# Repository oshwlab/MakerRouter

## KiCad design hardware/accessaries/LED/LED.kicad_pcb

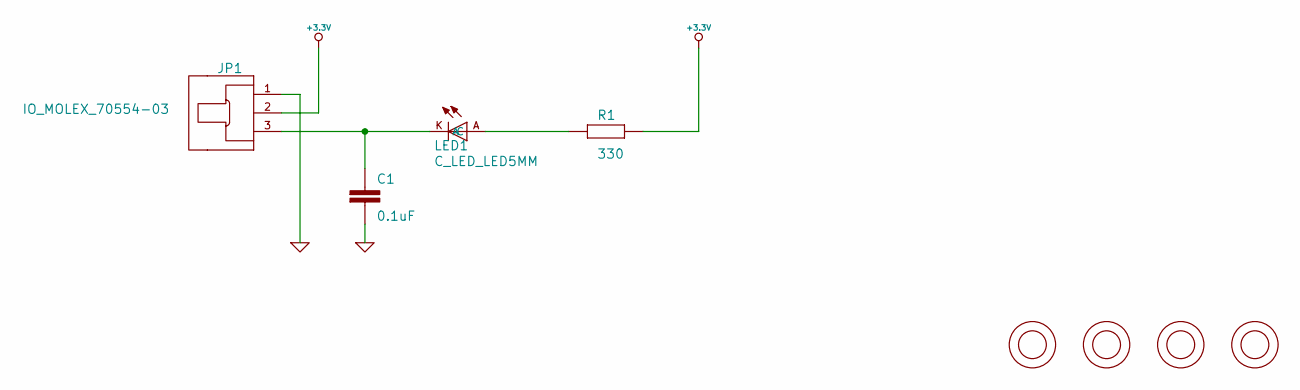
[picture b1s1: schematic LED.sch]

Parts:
C1: 0.1uF; C_C_0805
JP1: IO_MOLEX_70554-03
LED1: C_LED_LED5MM
P1, P2, P3, P4: IO_HOLE-3.2
R1: 330; C_R_0805

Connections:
+3.3V: JP1.2, R1.2
GND: C1.2, JP1.1
unnamed: LED1.A, R1.1
unnamed: C1.1, JP1.3, LED1.K (C)

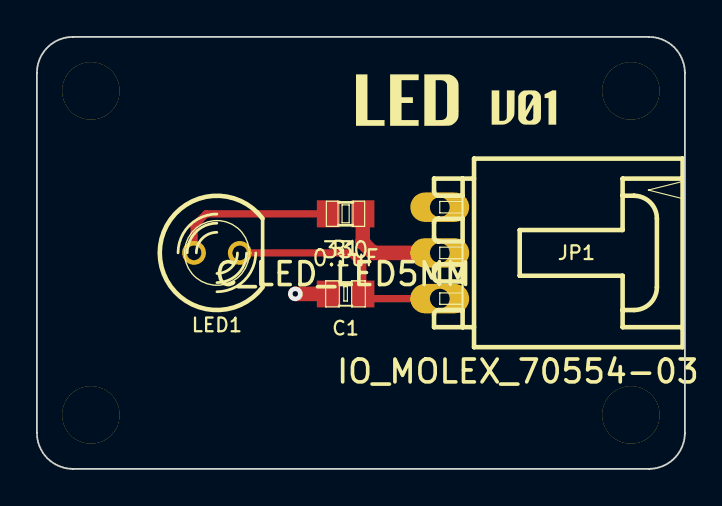
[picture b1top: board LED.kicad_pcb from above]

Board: 2 copper layers, 36.0 x 24.0 mm, 9 parts (1 on the bottom side), 4 nets.

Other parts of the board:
VAL: mini6

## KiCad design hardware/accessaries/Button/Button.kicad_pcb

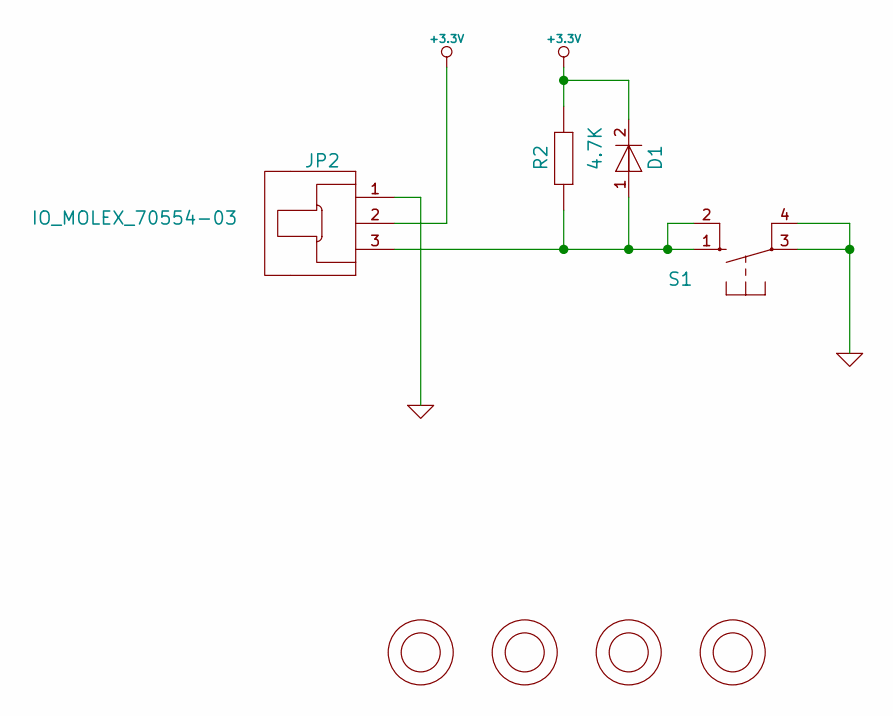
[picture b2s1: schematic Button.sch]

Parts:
D1: C_DIODE-1N4148_MINIMELF
JP2: IO_MOLEX_70554-03
P5, P6, P7, P8: IO_HOLE-3.2
R2: 4.7K; C_R_0805
S1: C_SW_OMRON-10-XX; switch-omron-B3F-40XX

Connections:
+3.3V: D1.2, JP2.2, R2.2
GND: JP2.1, S1.3, S1.4
unnamed: D1.1, JP2.3, R2.1, S1.1, S1.2

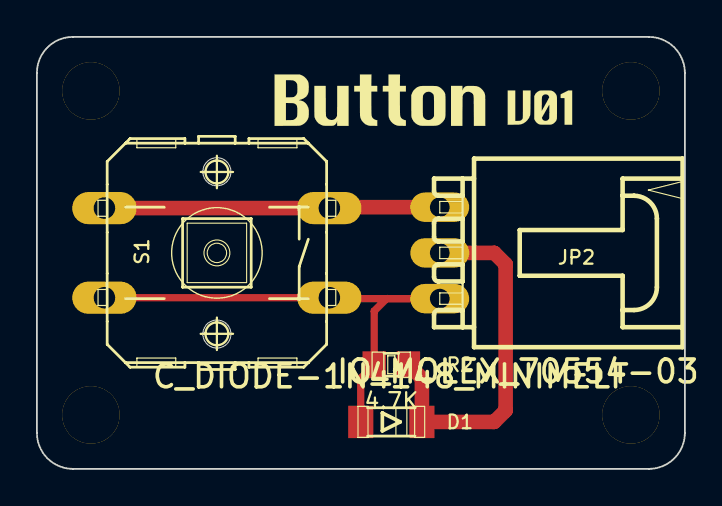
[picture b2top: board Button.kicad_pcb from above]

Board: 2 copper layers, 36.0 x 24.0 mm, 9 parts (1 on the bottom side), 3 nets.

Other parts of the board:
VAL: mini6

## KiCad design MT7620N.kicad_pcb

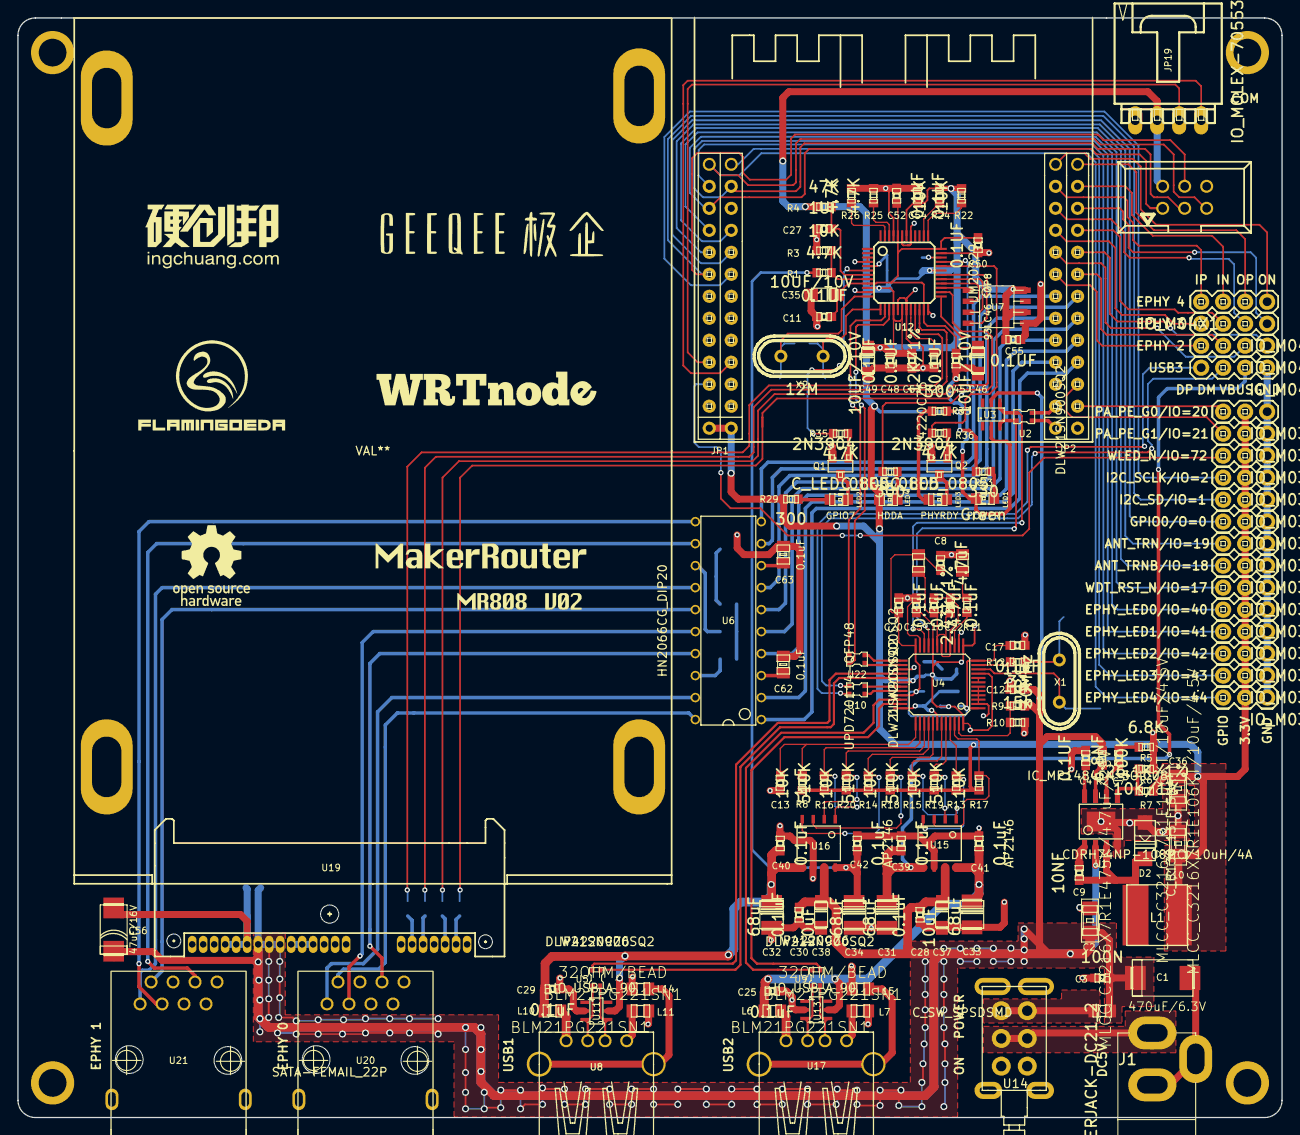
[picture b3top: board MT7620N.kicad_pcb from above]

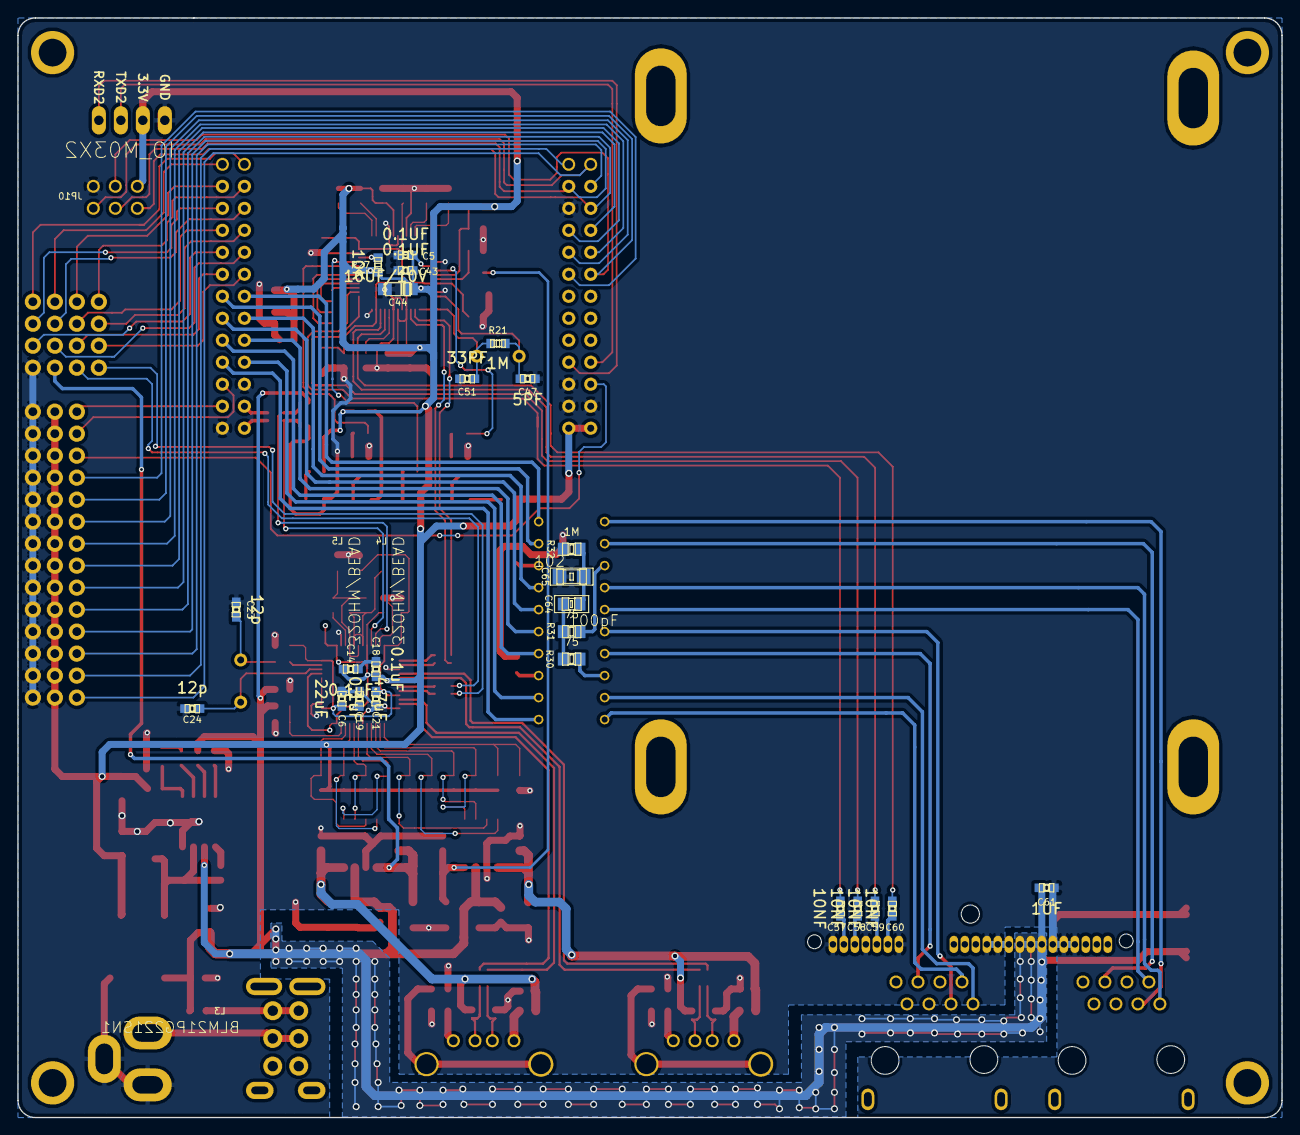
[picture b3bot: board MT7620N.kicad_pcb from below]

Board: 2 copper layers, 146.0 x 127.0 mm, 173 parts (24 on the bottom side), 144 nets.

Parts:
C1: 470uF/6.3V; C_CPOL_SMCE
C2: MLCC_C3216X7R1E475K/4.7uF/25V; rcl-C1206
C3: 100N; C_C_0603
C4, C5, C11, C43, C45, C48, C50, C52, C53, C54, C55: 0.1UF; C_C_0603
C6: 22uF; C_C_0603
C7: 6.8NF; C_C_0603
C8, C16, C19: 4.7uF; C_C_0603
C9, C57, C58, C59, C60: 10NF; C_C_0603
C10, C36: MLCC_C3216X7R1E106KT/10uF/4.5V; rcl-C1206
C12, C13: 1uF; C_C_0603
C14, C15, C17, C18, C20, C21, C22, C25, C28, C29, C30, C39, C40, C41, C42: 0.1uF; C_C_0603
C23, C24: 12p; C_C_0603
C27, C61: 1UF; C_C_0603
C31, C32, C33, C34: 68uF; C_CPOL_SMCB
C35, C44, C46, C49: 10UF/10V; C_CPOL_SMCA
C37, C38: 10uF; C_CPOL_SMCA
C47: 5PF; C_C_0603
C51: 33PF; C_C_0603
C56: 47uF/16V; C_CPOL_SMCC
C62, C63: 0.1uF; C_C_0805
C64: 100pF; rcl-C0805
C65: 102; rcl-C1206
D2: C_B130_13_F_SMA; C_B130
Hard-Disk: VAL**; Hard-Disk
J1: POWERJACK-DC21_2; POWERJACK-DC-2,1MM
JP1, JP2: IO_FM13X2
JP3, JP7, JP8, JP15, JP16, JP21, JP23, JP29, JP34, JP35, JP36, JP37, JP38, JP39: IO_M03X1
JP4, JP5, JP6, JP9: IO_M04X1
JP10: IO_M03X2; -CON-PANDUIT_057-006-1
JP19: IO_MOLEX-70553-04
L1: CDRH74NP-100MC/10uH/4A; rcl-L7070
L3, L6, L7, L10, L11: BLM21PG221SN1; rcl-L0805
L4, L5, L14, L15: 32OHM/BEAD; rcl-L0805
LED1: Green; C_LED_0805
LED2, LED3, LED4: C_LED_0805
P2, P6, P7, P8: IO_HOLE-3.2-BIG; IO_HOLE-3.2-big
Q1, Q2: 2N3904; C_T-NPN-BC847-SMD_SOT23
R1, R25, R26, R35, R36: 4.7K; C_R_0603
R2: 100K; C_R_0603
R3, R8, R17, R18, R19, R20, R22, R24, R27: 10K; C_R_0603
R4: 47K; C_R_0603
R5: 6.8K; C_R_0603
R6: 10K/1%; C_R_0603
R7: 26.1K/1%; C_R_0603
R9: 10k; C_R_0603
R10: 15k; C_R_0603
R11: 2.43k/1%; C_R_0603
R12: 33; C_R_0603
R13, R14, R15, R16: 510K; C_R_0603
R21: 1M; C_R_0603
R23: 330; C_R_0603
R28: 12K/1%; C_R_0603
R29, R33, R34: 300; C_R_0603
R30, R31: 75; C_R_0805
R32: 1M; C_R_0805
U1: IC_MP1484EN_SOIC08
U2, U5, U9, U10, U22: DLW21SN900SQ2
U3, U11, U13: IP4220CZ6; IP4220CZ6_SOT23_6
U4: UPD720114-QFP48
U6: HN2066CG_DIP20
U7: 93LC46_SOP8; SOP08
U8, U17: IO_USB_A_90
U12: JM20329; LQFP48
U14: C_SW_SPSDSMD; switchlock
U15, U16: AP2146; AP1212_SOP8
U19: SATA-FEMAIL_22P
U20, U21: IO_RJ45X1-JACK; IO_RJ45X1-8P8C-90
VAL: mini6
VAL#2: REF; opensouce
VAL#3: REF; ycb_V01
VAL#4: REF; GEEQEE2
VAL#5: REF; WRTnode
X1: 30MHz; C_CRY_DIP2
X2: 12M; C_CRY_DIP2

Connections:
+3.3V: C5.1, C10.1, C14.1, C15.1, C18.1, C19.1, C36.1, C43.1, C44.1, C48.1, C49.1, C53.1, C54.1, C55.1, JP1.1, JP1.2, JP3.2, JP7.2, JP8.2, JP10.2, JP15.2, JP16.2, JP19.2, JP21.2, JP23.2, JP29.2, JP34.2, JP35.2, JP36.2, JP37.2, JP38.2, JP39.2, L1.2, LED4.1, R4.2, R7.1, R8.2, R13.2, R14.2, R15.2, R16.2, R17.2, R18.2, R19.2, R20.2, R22.1, R23.1, R24.1, R27.2, R29.1, R33.1, U4.9, U4.13, U4.20, U4.30, U4.48, U7.6, U7.8, U12.5, U12.10, U12.16, U12.18, U12.31, U12.42
+5V: C1.1, C2.1, C3.1, C12.1, C28.1, C30.1, C37.1, C38.1, C56.1, C61.1, L3.2, R2.2, R9.1, U1.2, U3.5, U15.7, U16.7, U19.14, U19.15, U19.16
/ANT_TRN: JP1.18, JP38.3
/ANT_TRNB: JP1.19, JP39.3
/GPIO0: JP1.17, JP34.3
/I2C_SCLK: JP1.15, JP16.3
/I2C_SD: JP1.16, JP10.4, JP15.3
/LINK0: JP1.22, JP10.1, JP23.3
/LINK1: JP1.23, JP3.3, JP10.3
/LINK2: JP1.24, JP7.3
/LINK3: JP1.25, JP8.3
/LINK4: JP1.26, JP10.5, JP29.3
/PA_PE_G0: JP2.3, JP35.3
/PA_PE_G1: JP2.5, JP36.3
/RXD2: JP1.7, JP19.4
/RXIN2: JP2.15, JP6.3
/RXIN3: JP2.19, JP4.3
/RXIN4: JP2.23, JP5.3
/RXIP2: JP2.16, JP6.4
/RXIP3: JP2.20, JP4.4
/RXIP4: JP2.24, JP5.4
/SATA/AVREG: C11.1, C35.1, C45.1, C46.1, C50.1, C52.1, U12.9, U12.23, U12.36, U12.44
/SATA/DM: U12.14, U22.3
/SATA/DP: U12.15, U22.2
/SATA/GPIO0: U7.4, U12.30
/SATA/GPIO1: U7.3, U12.29
/SATA/GPIO2: U7.2, U12.28
/SATA/GPIO3: U7.1, U12.27
/SATA/GPIO7: R35.1, U12.6
/SATA/HDDA: R34.1, U12.33
/SATA/PHYRDY: R36.1, U12.32
/SATA/RESETn: C27.1, R4.1, U12.7
/SATA/RXN: C59.1, U12.22
/SATA/RXP: C60.1, U12.21
/SATA/TXN: C58.1, U12.25
/SATA/TXP: C57.1, U12.26
/SATA/VBUS: R1.1, R3.1, U12.8
/SATA/XTALI: C47.1, R21.2, U12.12, X2.1
/SATA/XTALO: C51.1, R21.1, U12.13, X2.2
/TXD2: JP1.8, JP19.3
/TXON2: JP2.17, JP6.1
/TXON3: JP2.21, JP4.1
/TXON4: JP2.26, JP5.1
/TXOP2: JP2.18, JP6.2
/TXOP3: JP2.22, JP4.2
/TXOP4: JP2.25, JP5.2
/WDT_RST_N: JP1.20, JP21.3
/WLAN/RXIN0: JP2.7, U6.1
/WLAN/RXIN1: JP2.11, U6.6
/WLAN/RXIP0: JP2.8, U6.2
/WLAN/RXIP1: JP2.12, U6.7
/WLAN/TXON0: JP2.9, U6.4
/WLAN/TXON1: JP2.13, U6.9
/WLAN/TXOP0: JP2.10, U6.5
/WLAN/TXOP1: JP2.14, U6.10
/WLED_N: JP1.6, JP37.3
/uPD720114/D+: JP2.4, U2.4
/uPD720114/D-: JP2.2, U2.1
/uPD720114/VBUS1: C31.1, C39.1, JP9.3, U15.5
/uPD720114/VBUS2: C25.1, C33.1, C41.1, L6.1, U13.5, U15.8
/uPD720114/VBUS3: C29.1, C32.1, C40.1, L10.1, U11.5, U16.5
/uPD720114/VBUS4: C34.1, C42.1, R1.2, U16.8
GND: C1.2, C2.2, C3.2, C4.1, C5.2, C6.1, C8.2, C10.2, C11.2, C12.2, C13.1, C14.2, C15.2, C17.2, C18.2, C19.2, C20.2, C21.2, C23.2, C24.2, C25.2, C27.2, C28.2, C29.2, C30.2, C31.2, C32.2, C33.2, C34.2, C35.2, C36.2, C37.2, C38.2, C39.2, C40.2, C41.2, C42.2, C43.2, C44.2, C45.2, C46.2, C47.2, C48.2, C49.2, C50.2, C51.2, C52.2, C53.2, C54.2, C55.2, C56.2, C61.2, C62.2, C63.2, C65.2, D2.A, J1.1, J1.3, JP1.3, JP1.4, JP1.5, JP1.21, JP2.1, JP2.6, JP3.1, JP7.1, JP8.1, JP9.4, JP10.6, JP15.1, JP16.1, JP19.1, JP21.1, JP23.1, JP29.1, JP34.1, JP35.1, JP36.1, JP37.1, JP38.1, JP39.1, L5.1, L7.1, L11.1, L14.2, L15.2, LED1.2, Q1.2, Q2.2, R3.2, R5.1, R6.2, R10.1, R25.1, R26.1, R28.2, R32.2, U1.4, U1.9, U3.2, U4.2, U4.3, U4.4, U4.5, U4.6, U4.14, U4.23, U4.27, U4.36, U4.42, U7.5, U11.2, U12.3, U12.4, U12.11, U12.17, U12.19, U12.24, U12.35, U12.41, U12.43, U12.45, U13.2, U15.6, U16.6, U19.1, U19.4, U19.7, U19.11, U19.12, U19.13, U19.17, U19.18, U19.19
unnamed: R17.1, U4.46, U15.3
unnamed: R19.1, U4.44, U15.2
unnamed: R18.1, U4.41, U16.3
unnamed: R16.1, U4.38, U16.1
unnamed: R14.1, U4.40, U16.4
unnamed: R20.1, U4.39, U16.2
unnamed: R12.1, U4.11
unnamed: U2.3, U3.4, U4.22
unnamed: U2.2, U3.3, U4.21
unnamed: R15.1, U4.43, U15.1
unnamed: R13.1, U4.45, U15.4
unnamed: L11.2, U8.4
unnamed: L10.2, U8.1
unnamed: L7.2, U17.4
unnamed: L6.2, U17.1
unnamed: U4.7, U4.8
unnamed: U5.2, U8.3, U11.4
unnamed: U4.32, U10.1
unnamed: U5.3, U8.2, U11.3
unnamed: U4.31, U10.4
unnamed: U9.3, U13.3, U17.2
unnamed: U9.2, U13.4, U17.3
unnamed: U4.28, U5.4
unnamed: U4.29, U5.1
unnamed: U4.26, U22.1
unnamed: U4.34, U9.4
unnamed: U4.35, U9.1
unnamed: JP9.2, U10.3
unnamed: JP9.1, U10.2
unnamed: U4.25, U22.4
unnamed: R11.2, U4.15
unnamed: R9.2, R10.2, U4.47
unnamed: C13.2, R8.1, U4.37
unnamed: C24.1, U4.10, X1.2
unnamed: C23.1, R12.2, X1.1
unnamed: C16.2, C22.2, L5.2, R11.1, U4.16, U4.18
unnamed: L15.1, U17.5, U17.6
unnamed: L14.1, U8.5, U8.6
unnamed: C16.1, C22.1, L4.2, U4.17, U4.19
unnamed: C6.2, C8.1, C17.1, C20.1, C21.1, L4.1, U4.1, U4.12, U4.24, U4.33
unnamed: C63.1, U6.8
unnamed: C62.1, U6.3
unnamed: U6.16, U20.3
unnamed: U6.20, U20.2
unnamed: U6.19, U20.1
unnamed: R30.1, U6.18
unnamed: U6.17, U20.6
unnamed: R31.1, U6.13
unnamed: C64.2, C65.1, R32.1
unnamed: C64.1, R30.2, R31.2
unnamed: U6.12, U21.6
unnamed: U6.11, U21.3
unnamed: U6.14, U21.1
unnamed: U6.15, U21.2
unnamed: R28.1, U12.20
unnamed: R25.2, U12.46
unnamed: R26.2, U12.47
unnamed: R22.2, U12.37
unnamed: R24.2, U12.38
unnamed: R27.1, U12.34
unnamed: C58.2, U19.3
unnamed: C59.2, U19.5
unnamed: C60.2, U19.6
unnamed: LED4.2, R34.2
unnamed: C57.2, U19.2
unnamed: LED3.1, R33.2
unnamed: LED3.2, Q2.3
unnamed: Q2.1, R36.2
unnamed: LED2.1, R29.2
unnamed: LED2.2, Q1.3
unnamed: Q1.1, R35.2
unnamed: C9.1, U1.1
unnamed: R2.1, U1.7
unnamed: C4.2, U1.8
unnamed: LED1.1, R23.2
unnamed: J1.2, U14.2, U14.5
unnamed: L3.1, U14.3, U14.6
unnamed: C7.2, U1.6
unnamed: C7.1, R5.2
unnamed: C9.2, D2.C, L1.1, U1.3
unnamed: R6.1, R7.2, U1.5

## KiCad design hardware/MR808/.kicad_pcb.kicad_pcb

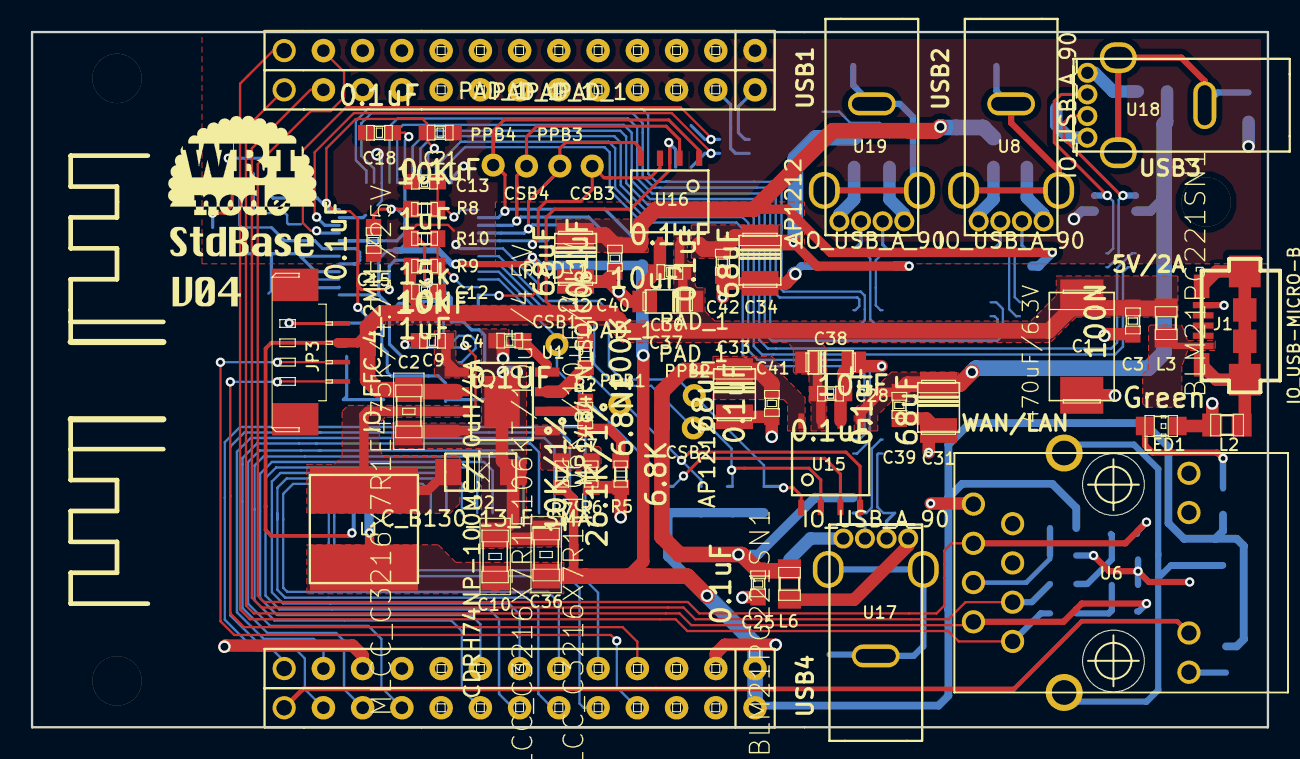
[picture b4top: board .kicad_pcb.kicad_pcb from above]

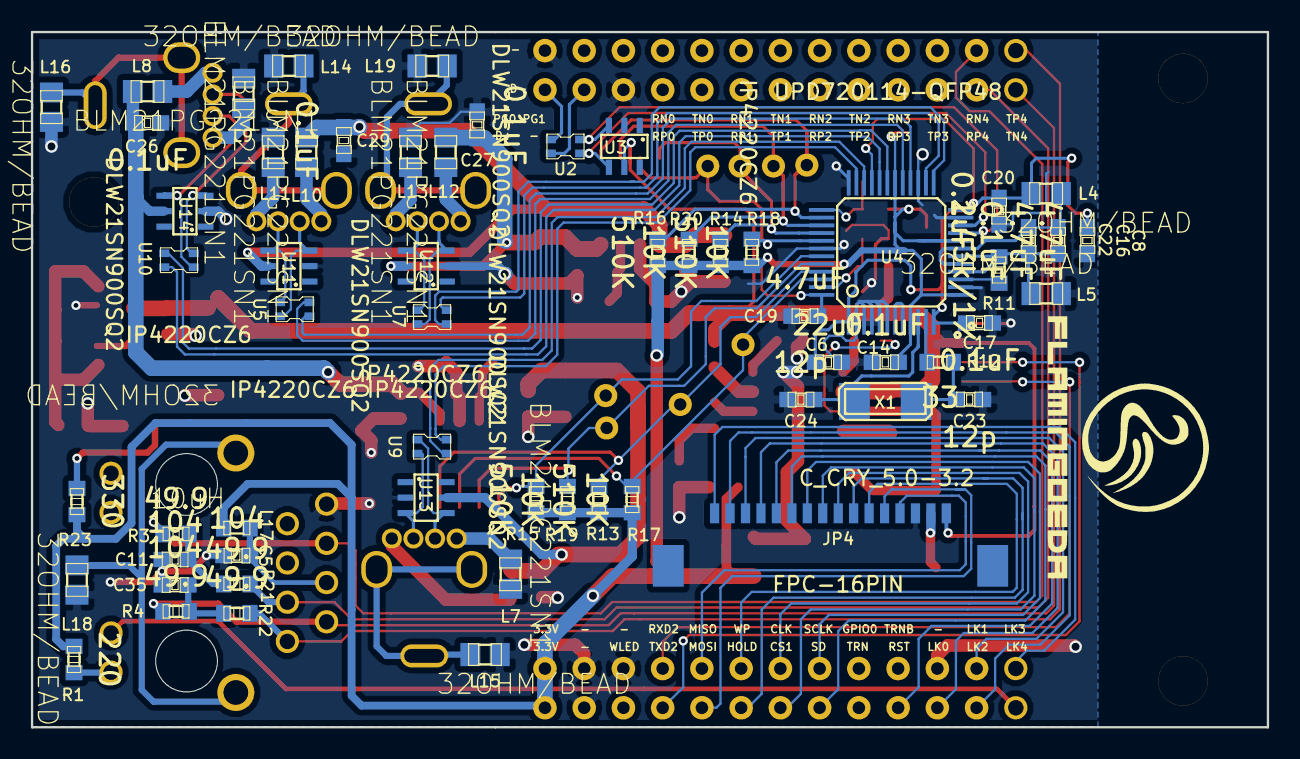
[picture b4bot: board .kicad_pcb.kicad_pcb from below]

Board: 2 copper layers, 80.0 x 45.0 mm, 124 parts (61 on the bottom side), 92 nets.

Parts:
C1: 470uF/6.3V; C_CPOL_SMCE
C2: MLCC_C3216X7R1E475K/4.7uF/25V; rcl-C1206
C3: 100N; C_C_0603
C4: 0.1UF; C_C_0603
C5, C11, C35: 104; C_C_0603
C6: 22uF; C_C_0603
C7: 6.8NF; C_C_0603
C8, C16, C19: 4.7uF; C_C_0603
C9: 10NF; C_C_0603
C10, C36: MLCC_C3216X7R1E106KT/10uF/4.5V; rcl-C1206
C12, C13: 1uF; C_C_0603
C14, C15, C17, C18, C20, C21, C22, C25, C26, C27, C28, C29, C30, C39, C40, C41, C42: 0.1uF; C_C_0603
C23, C24: 12p; C_C_0603
C31, C32, C33, C34: 68uF; C_CPOL_SMCB
C37, C38: 10uF; C_CPOL_SMCA
D2: C_B130_13_F_SMA; C_B130
J1: IO_USB-MICRO-B; IO_USB-MICRO-B-B
JP1, JP2: IO_FM13X2
JP3: IO_FFC_4_2MM
JP4: FPC-16PIN
L1: CDRH74NP-100MC/10uH/4A; rcl-L7070
L2, L4, L5, L14, L15, L16, L18, L19: 32OHM/BEAD; rcl-L0805
L3, L6, L7, L8, L9, L10, L11, L12, L13: BLM21PG221SN1; rcl-L0805
L17: 10uH; rcl-L0603
LED1: Green; C_LED_0805
P2, P3: IO_HOLE-3.2
P3#2: PINHOLE; IO_HOLE-3.2
P6, P6#2, P6#3, P6#4, P6#5, P6#6, P6#7, P6#8: PAD_1
R1: 220; C_R_0603
R2: 100K; C_R_0603
R3, R4, R21, R22: 49.9; C_R_0603
R5: 6.8K; C_R_0603
R6: 10K/1%; C_R_0603
R7: 26.1K/1%; C_R_0603
R8, R17, R18, R19, R20: 10K; C_R_0603
R9: 10k; C_R_0603
R10: 15k; C_R_0603
R11: 2.43k/1%; C_R_0603
R12: 33; C_R_0603
R13, R14, R15, R16: 510K; C_R_0603
R23: 330; C_R_0603
U1: IC_MP1484EN_SOIC08
U2, U5, U7, U9, U10: DLW21SN900SQ2
U3, U11, U12, U13, U14: IP4220CZ6; IP4220CZ6_SOT23_6
U4: UPD720114-QFP48
U6: HR911105A
U8, U17, U18, U19: IO_USB_A_90; IO-USB-A
U15, U16: AP1212; AP1212_SOP8
VAL: mini6
VAL#2: WRTNode
X1: C_CRY_5.0-3.2

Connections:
+3.3V: C10.1, C14.1, C15.1, C18.1, C19.1, C36.1, JP1.1, JP1.2, JP4.2, L1.2, L17.2, R1.2, R7.1, R8.2, R13.2, R14.2, R15.2, R16.2, R17.2, R18.2, R19.2, R20.2, R23.1, U4.9, U4.13, U4.20, U4.30, U4.48
+5V: C1.1, C2.1, C3.1, C12.1, C28.1, C30.1, C37.1, C38.1, JP3.2, JP4.1, L3.2, R2.2, R9.1, U1.2, U3.5, U15.7, U16.7
/I2C_SCLK: JP1.15, JP4.10
/I2C_SD: JP1.16, JP4.11
/LINK0: JP1.22, JP4.13
/LINK1: JP1.23, JP4.14
/LINK2: JP1.24, JP4.15
/LINK3: JP1.25, JP4.16
/LINK4: JP1.26, U6.10
/RXD2: JP1.7, JP3.4
/RXIN4: JP2.23, R3.2, U6.6
/RXIP4: JP2.24, R21.1, U6.3
/SPI_CLK: JP1.13, JP4.8
/SPI_CS1: JP1.14, JP4.9
/SPI_HOLD: JP1.12, JP4.7
/SPI_MISO: JP1.9, JP4.4
/SPI_MOSI: JP1.10, JP4.5
/SPI_WP: JP1.11, JP4.6
/TXD2: JP1.8, JP3.3
/TXON4: JP2.26, R4.2, U6.2
/TXOP4: JP2.25, R22.1, U6.1
/WDT_RST_N: JP1.20, JP4.12
/uPD720114/D+: JP2.4, U2.4
/uPD720114/D-: JP2.2, U2.1
/uPD720114/VBUS1: C26.1, C31.1, C39.1, L8.1, U14.5, U15.5
/uPD720114/VBUS2: C25.1, C33.1, C41.1, L6.1, U13.5, U15.8
/uPD720114/VBUS3: C29.1, C32.1, C40.1, L10.1, U11.5, U16.5
/uPD720114/VBUS4: C27.1, C34.1, C42.1, L12.1, U12.5, U16.8
GND: C1.2, C2.2, C3.2, C4.1, C5.2, C6.1, C8.2, C10.2, C11.2, C12.2, C13.1, C14.2, C15.2, C17.2, C18.2, C19.2, C20.2, C21.2, C23.2, C24.2, C25.2, C26.2, C27.2, C28.2, C29.2, C30.2, C31.2, C32.2, C33.2, C34.2, C35.2, C36.2, C37.2, C38.2, C39.2, C40.2, C41.2, C42.2, D2.A, J1.P5, JP1.3, JP1.4, JP1.5, JP1.21, JP2.1, JP2.6, JP3.1, JP4.3, L2.2, L5.1, L7.1, L9.1, L11.1, L13.1, L14.2, L15.2, L16.2, L18.2, L19.2, LED1.2, R5.1, R6.2, R10.1, U1.4, U1.9, U3.2, U4.2, U4.3, U4.4, U4.5, U4.6, U4.14, U4.23, U4.27, U4.36, U4.42, U6.8, U11.2, U12.2, U13.2, U14.2, U15.6, U16.6
unnamed: C9.1, U1.1
unnamed: R2.1, U1.7
unnamed: C9.2, D2.C, L1.1, U1.3
unnamed: R6.1, R7.2, U1.5
unnamed: C7.1, R5.2
unnamed: C7.2, U1.6
unnamed: C4.2, U1.8
unnamed: J1.S1, J1.S2, J1.S3, J1.S4, J1.S5, J1.S6, L2.1
unnamed: C11.1, R3.1, R21.2
unnamed: C35.1, R4.1, R22.2
unnamed: LED1.1, R23.2
unnamed: L18.1, U6.13, U6.14
unnamed: R1.1, U6.9
unnamed: J1.P1, L3.1
unnamed: C5.1, L17.1, U6.4
unnamed: P6#2.1, R19.1, U4.44, U15.2
unnamed: P6#4.1, R17.1, U4.46, U15.3
unnamed: P6.1, R15.1, U4.43, U15.1
unnamed: P6#3.1, R13.1, U4.45, U15.4
unnamed: P6#6.1, R20.1, U4.39, U16.2
unnamed: P6#8.1, R18.1, U4.41, U16.3
unnamed: P6#5.1, R16.1, U4.38, U16.1
unnamed: P6#7.1, R14.1, U4.40, U16.4
unnamed: R9.2, R10.2, U4.47
unnamed: C13.2, R8.1, U4.37
unnamed: U2.2, U3.3, U4.21
unnamed: R12.1, U4.11
unnamed: U2.3, U3.4, U4.22
unnamed: L7.2, U17.4
unnamed: L6.2, U17.1
unnamed: U4.25, U7.1
unnamed: L9.2, U18.4
unnamed: L8.2, U18.1
unnamed: U4.7, U4.8
unnamed: U7.3, U12.4, U19.3
unnamed: U7.2, U12.3, U19.2
unnamed: U5.2, U8.2, U11.3
unnamed: U4.32, U10.4
unnamed: L14.1, U8.5, U8.6, U8.7
unnamed: L19.1, U19.5, U19.6, U19.7
unnamed: U10.2, U14.3, U18.2
unnamed: U10.3, U14.4, U18.3
unnamed: U4.31, U10.1
unnamed: R11.2, U4.15
unnamed: U4.29, U5.4
unnamed: U9.2, U13.3, U17.2
unnamed: U9.3, U13.4, U17.3
unnamed: U4.28, U5.1
unnamed: U4.26, U7.4
unnamed: U4.34, U9.1
unnamed: U4.35, U9.4
unnamed: L10.2, U8.1
unnamed: L13.2, U19.4
unnamed: L11.2, U8.4
unnamed: L12.2, U19.1
unnamed: L15.1, U17.5, U17.6, U17.7
unnamed: L16.1, U18.5, U18.6, U18.7
unnamed: U5.3, U8.3, U11.4
unnamed: C23.1, R12.2, X1.1
unnamed: C24.1, U4.10, X1.2
unnamed: C6.2, C8.1, C17.1, C20.1, C21.1, L4.1, U4.1, U4.12, U4.24, U4.33
unnamed: C16.2, C22.2, L5.2, R11.1, U4.16, U4.18
unnamed: C16.1, C22.1, L4.2, U4.17, U4.19

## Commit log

2014-12-23 添加文件并整理目录
2014-12-24 添加原理图PDF文档
2014-12-26 整理目录
2014-12-30 新修改布局
2015-01-06 完成新要求修改，生成gerber文件
2015-01-22 MakerRouter第二版本生成gerber
2015-01-26 更新schematic.pdf
2015-02-15 Add littleboard PCB
2015-02-15 Move MR808 to hardware directory.
2015-02-15 Add accessaries
2015-02-15 Add license documentation.
2015-02-26 Separate into two modules
